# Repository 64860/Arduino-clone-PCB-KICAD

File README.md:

Based on the comprehensive analysis of the repository, the project is classified as an **Electronic Design/Hardware Project**. It contains design files for a breadboard power supply created using the KiCAD EDA suite.

The repository lacks typical software components like programming languages, frameworks, databases, or build tools. Instead, it comprises KiCAD project files, schematic and PCB layout files, backup data, cache files, and generated output documents and images.

---

# 🔌 Breadboard Power Supply (KiCAD)

<div align="center">

 <!-- Main project image -->

**A versatile and compact power supply designed for breadboard prototyping, fully open-source with KiCAD files.**

</div>

## 📖 Overview

This repository contains the complete KiCAD design files for a breadboard power supply module. It's engineered to provide stable and regulated power rails, typically 3.3V and 5V, directly to your breadboard, making it an essential tool for electronics prototyping and development. The design focuses on reliability, ease of use, and integration, offering a convenient way to power your circuits without needing external bench power supplies.

All design files, including schematics and PCB layouts, are provided, allowing users to inspect, modify, and fabricate their own breadboard power supplies.

## ✨ Features

-   🎯 **Dual Voltage Output:** Provides commonly used regulated DC outputs (e.g., 3.3V and 5V) for versatile prototyping.
-   ⚡ **Standard Power Input:** Designed for common power input sources (e.g., DC barrel jack, USB), offering flexibility.
-   💡 **Power Indicator LED:** An onboard LED clearly indicates when the module is powered.
-   🛡️ **Protection Circuitry:** Includes basic protection (e.g., reverse polarity, current limiting) to safeguard your circuits and the power supply.
-   📏 **Compact & Breadboard Compatible:** Form factor designed to seamlessly integrate with standard breadboards, occupying minimal space.
-   🛠️ **Open Source Hardware:** Fully designed in KiCAD, allowing for easy customization and community contributions.

## 🖥️ Screenshots

| Overall View | PCB Render 1 | PCB Render 2 | Schematic View |
| :----------: | :----------: | :----------: | :------------: |
|  |  |  |  |

## 🛠️ Tech Stack

This project is built using the following Electronic Design Automation (EDA) tools:

**EDA Software:**
-   

## 🚀 Quick Start

To view, modify, or fabricate this breadboard power supply, you will need the KiCAD EDA Suite.

### Prerequisites
-   **KiCAD EDA Suite:** Ensure you have KiCAD (version 6.0 or higher recommended) installed on your system.
    -   [Download KiCAD](https://www.kicad.org/download/)

### Installation

1.  **Clone the repository**
    ```bash
    git clone https://github.com/64860/Breadboard-power-supply-KiCAD-.git
    cd Breadboard-power-supply-KiCAD-
    ```

2.  **Open the project in KiCAD**
    -   Launch KiCAD.
    -   From the KiCAD Project Manager, select `File > Open Project...` (or `Project > Open Project...`).
    -   Navigate to the cloned repository directory and open the `Breadboard power supply.kicad_pro` file.

## 📁 Project Structure

The repository contains the following KiCAD project files and associated outputs:

```
project-root/
├── Breadboard power supply-backups/ # Directory for KiCAD automatic backups
├── Breadboard power supply.kicad_pcb # KiCAD PCB layout file
├── Breadboard power supply.kicad_prl # KiCAD project-specific library or preferences
├── Breadboard power supply.kicad_pro # KiCAD project definition file (main entry point)
├── Breadboard power supply.kicad_sch # KiCAD schematic diagram file
├── Breadboard power supply.kicad_sch-bak # Backup of the schematic file
├── Breadboard power supply1.png    # Screenshot/render of PCB (alternate view)
├── Breadboard power supply2.png    # Screenshot/render of PCB (alternate view)
├── Image.PNG                       # Main project image/render
├── Print PCB.pdf                   # PDF export of the PCB layout for printing/review
├── Print Schematic.pdf             # PDF export of the schematic for printing/review
├── README.md                       # This README file
├── fp-info-cache                   # KiCAD footprint information cache file
├── schematic.PNG                   # Screenshot of the schematic diagram
└── [~*.lck files]                  # KiCAD lock files (ignored in version control)
```

## ⚙️ Configuration

The project's configuration is embedded within the KiCAD design files (`.kicad_pro`, `.kicad_sch`, `.kicad_pcb`). All component values, footprints, and routing decisions are part of these files.

## 🚀 Manufacturing

To get the PCB manufactured:

1.  **Generate Gerbers:**
    -   Open `Breadboard power supply.kicad_pcb` in KiCAD's PCB Editor.
    -   Go to `File > Plot`.
    -   Select the desired output format (Gerber is standard) and layers.
    -   Generate the Gerber files, which can then be sent to a PCB fabrication house.

2.  **Review PDFs:**
    -   The `Print PCB.pdf` and `Print Schematic.pdf` files provide a convenient way to review the design without KiCAD, or to print for reference.

## 🤝 Contributing

We welcome contributions to improve this breadboard power supply design! If you have suggestions for enhancements, bug fixes, or new features, please feel free to:

1.  **Fork the repository.**
2.  **Create a new branch** for your changes.
3.  **Make your modifications** in KiCAD.
4.  **Commit your changes** with descriptive messages.
5.  **Open a Pull Request** explaining your changes.

Please ensure your contributions adhere to good KiCAD design practices and maintain clear documentation within the schematic and layout.

## 📄 License

This project is licensed under the [LICENSE_NAME](LICENSE) - see the LICENSE file for details. <!-- TODO: Specify actual license (e.g., MIT, CERN OHL) and create a LICENSE file -->

## 🙏 Acknowledgments

-   **KiCAD EDA Suite:** For providing an excellent open-source platform for electronic design.

## 📞 Support & Contact

If you have any questions, encounter issues, or need assistance, please feel free to:

-   🐛 **Open an Issue:** [GitHub Issues](https://github.com/64860/Breadboard-power-supply-KiCAD-/issues)
-   📧 **Email:** [contact@example.com] <!-- TODO: Add a contact email address -->

---

<div align="center">

**⭐ Star this repo if you find it helpful for your prototyping needs!**

Made with ❤️ by [Author Name] <!-- TODO: Add author's name or GitHub handle (e.g., @64860) -->

</div>

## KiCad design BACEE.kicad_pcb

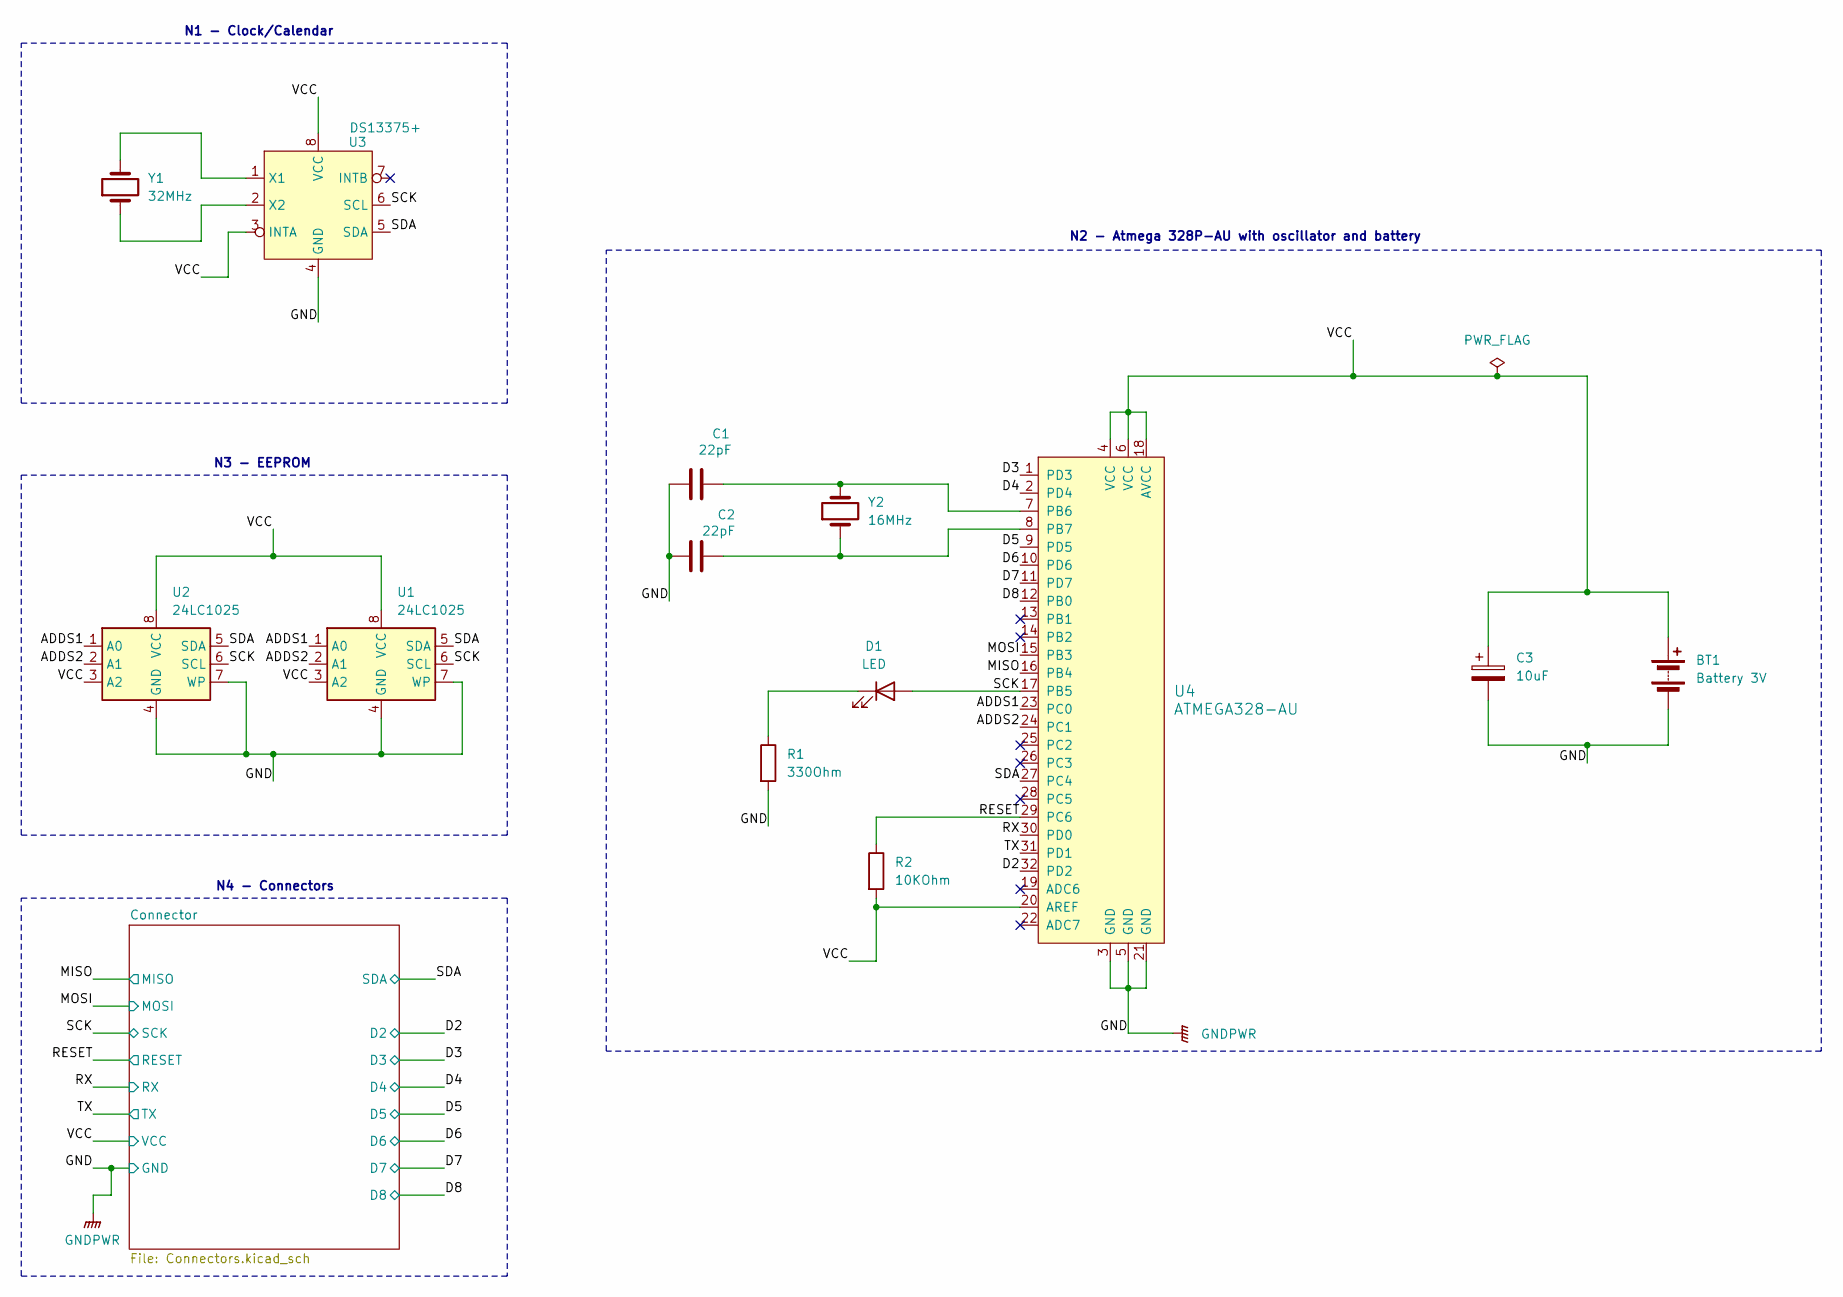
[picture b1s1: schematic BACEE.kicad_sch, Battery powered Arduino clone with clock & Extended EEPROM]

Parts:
BT1: Battery 3V; PinHeader_1x02_P2.54mm_Vertical
C1, C2: 22pF; C_0805_2012Metric_Pad1.18x1.45mm_HandSolder
C3: 10uF; C_0805_2012Metric_Pad1.18x1.45mm_HandSolder
D1: LED; LED_0805_2012Metric_Pad1.15x1.40mm_HandSolder
R1: 330Ohm; R_0805_2012Metric_Pad1.20x1.40mm_HandSolder
R2: 10KOhm; R_0805_2012Metric_Pad1.20x1.40mm_HandSolder
U1, U2: 24LC1025; SOIC-8_5.3x5.3mm_P1.27mm
U3: DS13375+; SOIC-8_3.9x4.9mm_P1.27mm
U4: ATMEGA328-AU; TQFP-32_7x7mm; MPN ATMEGA328-AU; Digi-Key_PN ATMEGA328-AU-ND
Y1: 32MHz; Crystal_SMD_MicroCrystal_CC7V-T1A-2Pin_3.2x1.5mm
Y2: 16MHz; Crystal_SMD_5032-2Pin_5.0x3.2mm_HandSoldering

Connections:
/ADDS1: U1.1 (A0), U2.1 (A0), U4.23 (PC0)
/ADDS2: U1.2 (A1), U2.2 (A1), U4.24 (PC1)
/D2: U4.32 (PD2); also elsewhere on the board
/D3: U4.1 (PD3); also elsewhere on the board
/D4: U4.2 (PD4); also elsewhere on the board
/D5: U4.9 (PD5); also elsewhere on the board
/D6: U4.10 (PD6); also elsewhere on the board
/D7: U4.11 (PD7); also elsewhere on the board
/D8: U4.12 (PB0); also elsewhere on the board
/MISO: U4.16 (PB4); also elsewhere on the board
/MOSI: U4.15 (PB3); also elsewhere on the board
/RESET: R2.1, U4.29 (PC6); also elsewhere on the board
/RX: U4.30 (PD0); also elsewhere on the board
/SCK: D1.2 (A), U1.6 (SCL), U2.6 (SCL), U3.6 (SCL), U4.17 (PB5); also elsewhere on the board
/SDA: U1.5 (SDA), U2.5 (SDA), U3.5 (SDA), U4.27 (PC4); also elsewhere on the board
/TX: U4.31 (PD1); also elsewhere on the board
/VCC: BT1.1 (+), C3.1, R2.2, U1.3 (A2), U1.8 (VCC), U2.3 (A2), U2.8 (VCC), U3.3 (INTA), U3.8 (VCC), U4.4 (VCC), U4.6 (VCC), U4.18 (AVCC), U4.20 (AREF); also elsewhere on the board
GNDPWR: BT1.2 (-), C1.1, C2.1, C3.2, R1.2, U1.4 (GND), U1.7 (WP), U2.4 (GND), U2.7 (WP), U3.4 (GND), U4.3 (GND), U4.5 (GND), U4.21 (GND); also elsewhere on the board
unnamed: D1.1 (K), R1.1
unnamed: U3.1 (X1), Y1.2
unnamed: U3.2 (X2), Y1.1
unnamed: C1.2, U4.7 (PB6), Y2.2
unnamed: C2.2, U4.8 (PB7), Y2.1

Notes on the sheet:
N2 - Atmega 328P-AU with oscillator and battery
N4 - Connectors
N1 - Clock/Calendar
N3 - EEPROM

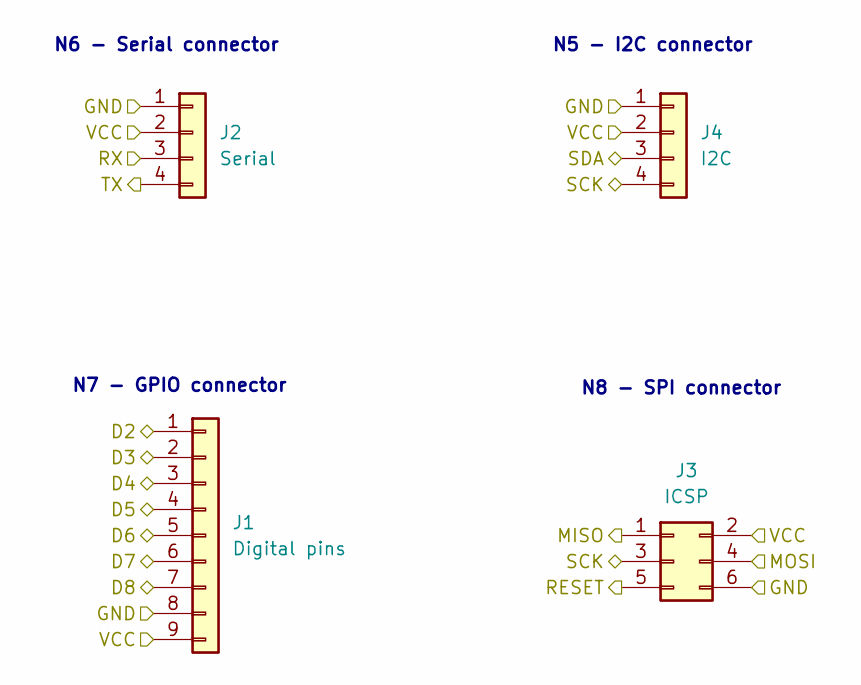
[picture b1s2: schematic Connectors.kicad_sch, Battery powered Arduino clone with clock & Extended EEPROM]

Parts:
J1: Digital pins; PinSocket_1x09_P2.54mm_Vertical
J2: Serial; PinSocket_1x04_P2.54mm_Vertical
J3: ICSP; PinSocket_2x03_P2.54mm_Vertical
J4: I2C; PinSocket_1x04_P2.54mm_Vertical

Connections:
/D2: J1.1; also elsewhere on the board
/D3: J1.2; also elsewhere on the board
/D4: J1.3; also elsewhere on the board
/D5: J1.4; also elsewhere on the board
/D6: J1.5; also elsewhere on the board
/D7: J1.6; also elsewhere on the board
/D8: J1.7; also elsewhere on the board
/MISO: J3.1; also elsewhere on the board
/MOSI: J3.4; also elsewhere on the board
/RESET: J3.5; also elsewhere on the board
/RX: J2.3; also elsewhere on the board
/SCK: J3.3, J4.4; also elsewhere on the board
/SDA: J4.3; also elsewhere on the board
/TX: J2.4; also elsewhere on the board
/VCC: J1.9, J2.2, J3.2, J4.2; also elsewhere on the board
GNDPWR: J1.8, J2.1, J3.6, J4.1; also elsewhere on the board

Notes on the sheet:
N8 - SPI connector
N6 - Serial connector
N5 - I2C connector
N7 - GPIO connector

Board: 2 copper layers, 17 parts (0 on the bottom side), 23 nets, no tracks yet.

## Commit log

2025-06-23 Setup the title block in the schematic sheet
2025-06-24 Created new child sheet, added project symbols
2025-06-24 Added symbol for ATMEGA328P-AU
2025-06-24 Added custom clock IC symbol
2025-06-24 Added missing crystals
2025-06-24 Arranged symbols
2025-06-24 Assigned the footprints
2025-06-28 Completed adding components values
2025-06-28 Completed wiring in child sheet
2025-07-02 Added power flags and corrected the GND
2025-07-02 Added functional block descriptions
2025-07-02 Started work in PCBNew.
2025-07-02 Set the design rules
2025-07-02 Created outline and mounting holes.
2025-07-04 Fully routed the board in 2 layers.
2025-07-04 Fully routed the board in 4 layers.
2025-07-04 Created Copper fill area for 2 layer board
2025-07-04 Did the silkscreen.
2026-02-17 Added images folder
2026-02-17 Create README.md for Arduino clone PCB project
    Add comprehensive README for Arduino clone PCB project.
2026-02-17 Revise README for Breadboard Power Supply project
    Updated README to reflect the new project focus on a breadboard power supply designed in KiCAD, including changes to project description, features, installation instructions, and contact information.
